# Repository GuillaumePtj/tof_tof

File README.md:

# tof_tof  

Projet Option Musique ENSEA : modification des caractéristiques d'un signal via l'utilisation d'un capteur ToF (Time to Fly) et ultrason  
Membres : Guillaume PORTEJOIE, Mathis HOCHMUTH, Antoine KERNEIS  

### Objectifs

* Ce système doit respecter les normes Eurorack pour pouvoir être monté sur rack. 
* Il doit être controlable par capteur ToF, pour jouer sur les tension de sortie avec des gestes.
* Il doit présenter des entrées jack ou avec potentiomètre pour piloter les offsets.

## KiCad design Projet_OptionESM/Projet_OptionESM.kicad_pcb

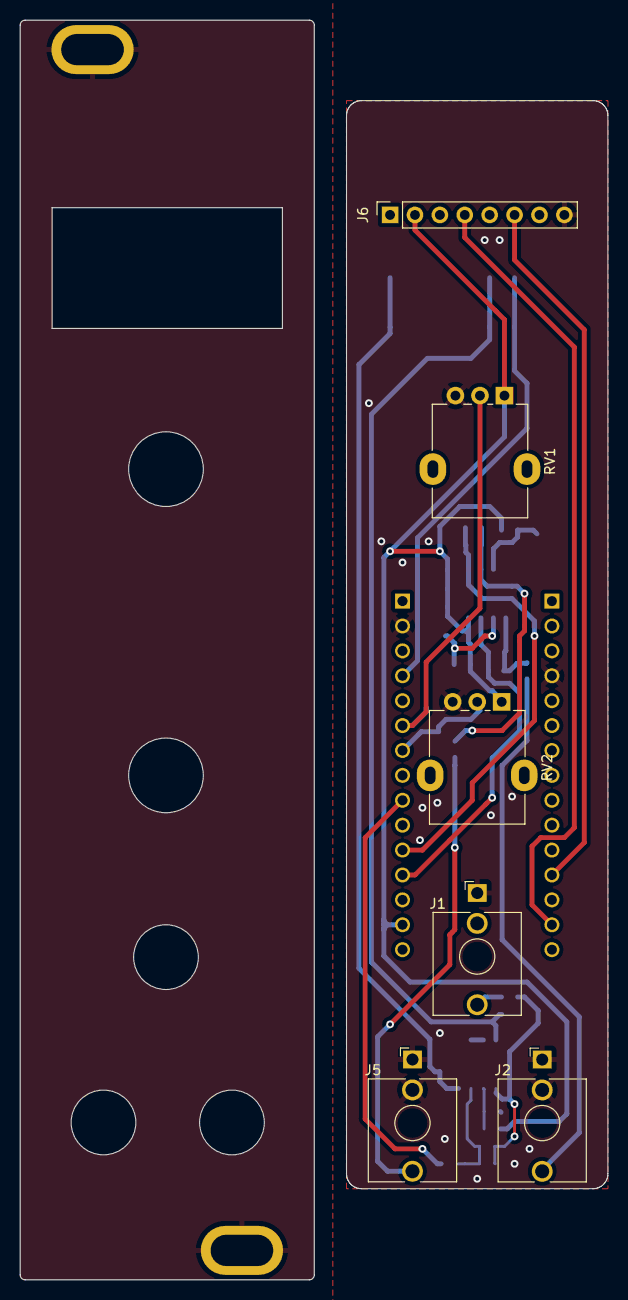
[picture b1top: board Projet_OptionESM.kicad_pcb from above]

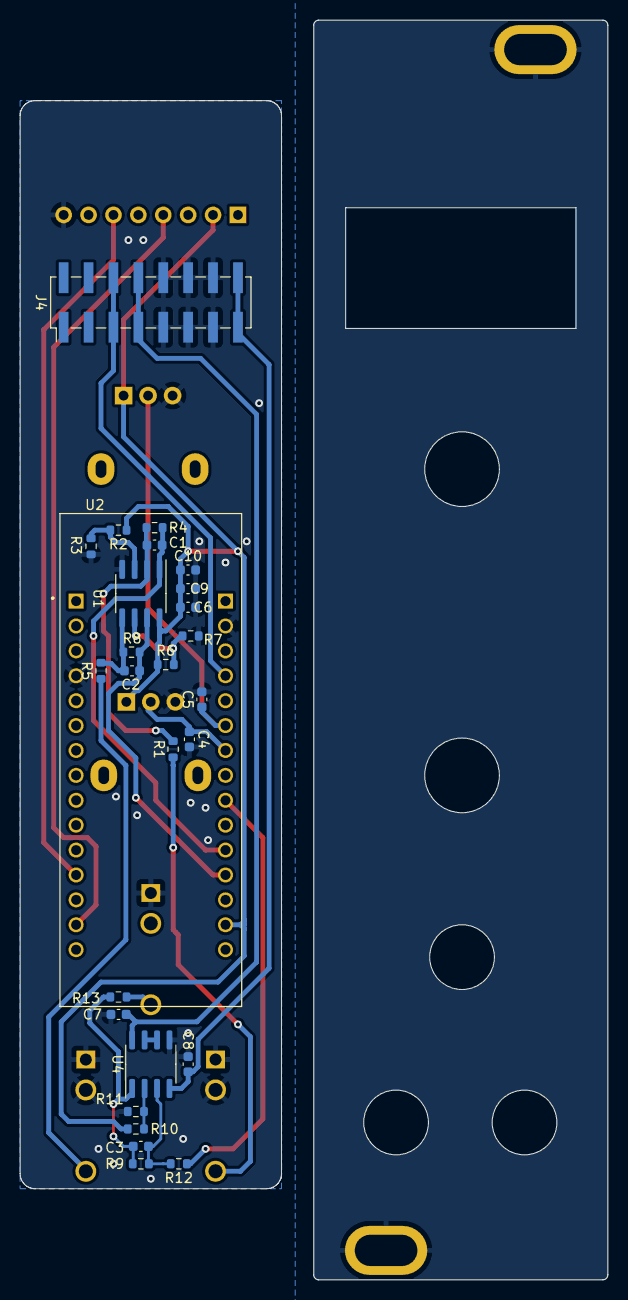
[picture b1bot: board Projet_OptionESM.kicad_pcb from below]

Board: 2 copper layers, 26.7 x 111.0 mm, 34 parts (27 on the bottom side), 23 nets.

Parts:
C1, C2: 270pF; C_0603_1608Metric
C3: 100p; C_0603_1608Metric
C4, C5, C6, C10: 100nF; C_0603_1608Metric
C7, C8: LIRE_LA_DOC; C_0603_1608Metric
C9: 1uF; C_0603_1608Metric
J1, J2, J5: AudioJack2_SwitchT; Jack_3.5mm_QingPu_WQP-PJ398SM_Vertical_CircularHoles
J4: POWER; PinHeader_2x08_P2.54mm_Vertical_SMD
J6: Conn_01x08; PinSocket_1x08_P2.54mm_Vertical
R1, R5: 200k; R_0603_1608Metric
R2, R6, R10: 36k; R_0603_1608Metric
R3, R7, R11: 27k; R_0603_1608Metric
R4, R8: 33k; R_0603_1608Metric
R9: 91k; R_0603_1608Metric
R12: 15k; R_0603_1608Metric
R13: 1k; R_0603_1608Metric
RV1, RV2: R_Potentiometer; Potentiometer_Alpha_RD901F-40-00D_Single_Vertical
U1: MCP6002-E/SN; SOIC-8_3.9x4.9mm_P1.27mm
U2: NUCLEO-G431KB; MODULE_NUCLEO-L432KC
U3: TOF; FACEPLATE_6HP
U4: TL072; SOIC-8_3.9x4.9mm_P1.27mm

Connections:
+3.3V: C6.1, C9.1, C10.1, J6.2, R2.1, R6.1, R10.1, RV1.1, RV2.1, U1.8 (V+), U2.CN4_14 (+3V3)
+5V: J4.5, J4.6, U2.CN4_4 (+5V)
+12V: C7.1, J4.7, J4.8, U4.8 (V+)
-12V: C8.2, J4.15, J4.16, U4.4 (V-)
/MCP1A+: R2.2, R3.2, U1.3 (+)
/MCP1A+6: R6.2, R7.2, U1.6 (-)
/MCP1A-: C1.1, R1.2, R4.1, U1.2 (-)
/MCP1A-5: C2.1, R5.2, R8.1, U1.5 (+)
ADC0: C2.2, R8.2, U1.7, U2.CN4_12 (PA0)
ADC1: C1.2, R4.2, U1.1, U2.CN4_11 (PA1)
ADC2: C4.1, RV2.2, U2.CN4_7 (PA6)
ADC3: C5.1, RV1.2, U2.CN4_6 (PA7)
DAC: R12.1, U2.CN4_9 (PA4)
GND: C4.2, C5.2, C6.2, C7.2, C8.1, C9.2, C10.2, J1.S, J2.S, J2.TN, J4.9, J4.10, J4.11, J4.12, J4.13, J4.14, J5.S, J5.TN, J6.8, R3.1, R7.1, R11.1, RV1.3, RV2.3, U1.4 (V-), U2.CN3_4 (GND_CN3), U2.CN4_2 (GND_CN4), U3.1 (GND), U4.5 (+)
unnamed: C3.2, R9.2, R13.1, U4.1
unnamed: J1.T, R13.2
unnamed: J2.T, R5.1
unnamed: J5.T, R1.1
unnamed: C3.1, R9.1, R12.2, U4.3 (+)
unnamed: R10.2, R11.2, U4.2 (-)
unnamed: U4.6 (-), U4.7
ToF-data: J6.4, U2.CN3_14 (PB5)
ToF_clk: J6.6, U2.CN3_12 (PA8)
